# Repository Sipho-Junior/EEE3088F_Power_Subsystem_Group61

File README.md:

# EEE3088F_Power_Subsystem_Group61 
The micro-mouse project requires the design and development of a compact, efficient, and reliable power subsystem capable of operating autonomously within a constrained embedded system.
This subsystem will be interfaced with the rest of the micro-mouse through a 2x16-pin header and a JST PH connector for the battery, designed to comply with the physical and electrical constraints specified in the project brief. 

This repository contains the design files and documentation for the power subsystem of an autonomous micro-mouse project developed for EEE3088F 2025. The micro-mouse is designed to navigate and solve mazes autonomously.

# System Architecture
The complete micro-mouse consists of four essential subsystems:

Motherboard - The foundation PCB connecting all other components
Processor Board - Features an STM32L476 microcontroller for computation and control
Sensing Subsystem - Equipped with distance sensors for environmental awareness
Power Subsystem - Focus of this repository

# Power Subsystem Features
The power subsystem is responsible for:

Providing stable 3.3V and 5V power to all micro-mouse components
Controlling up to 4 motors bidirectionally (2 main motors + 2 auxiliary)
Supporting external load switching (2 channels at 1A each)
Real-time power monitoring via INA219 on I2C bus
Battery management for a 1S1P LiPo battery (800mAh 3.7V)
Dual charging modes (200mA and 600mA±100mA)
USB-C power input with 9V Power Delivery negotiation
Power system ON/OFF control with ultra-low standby current (<30μA)

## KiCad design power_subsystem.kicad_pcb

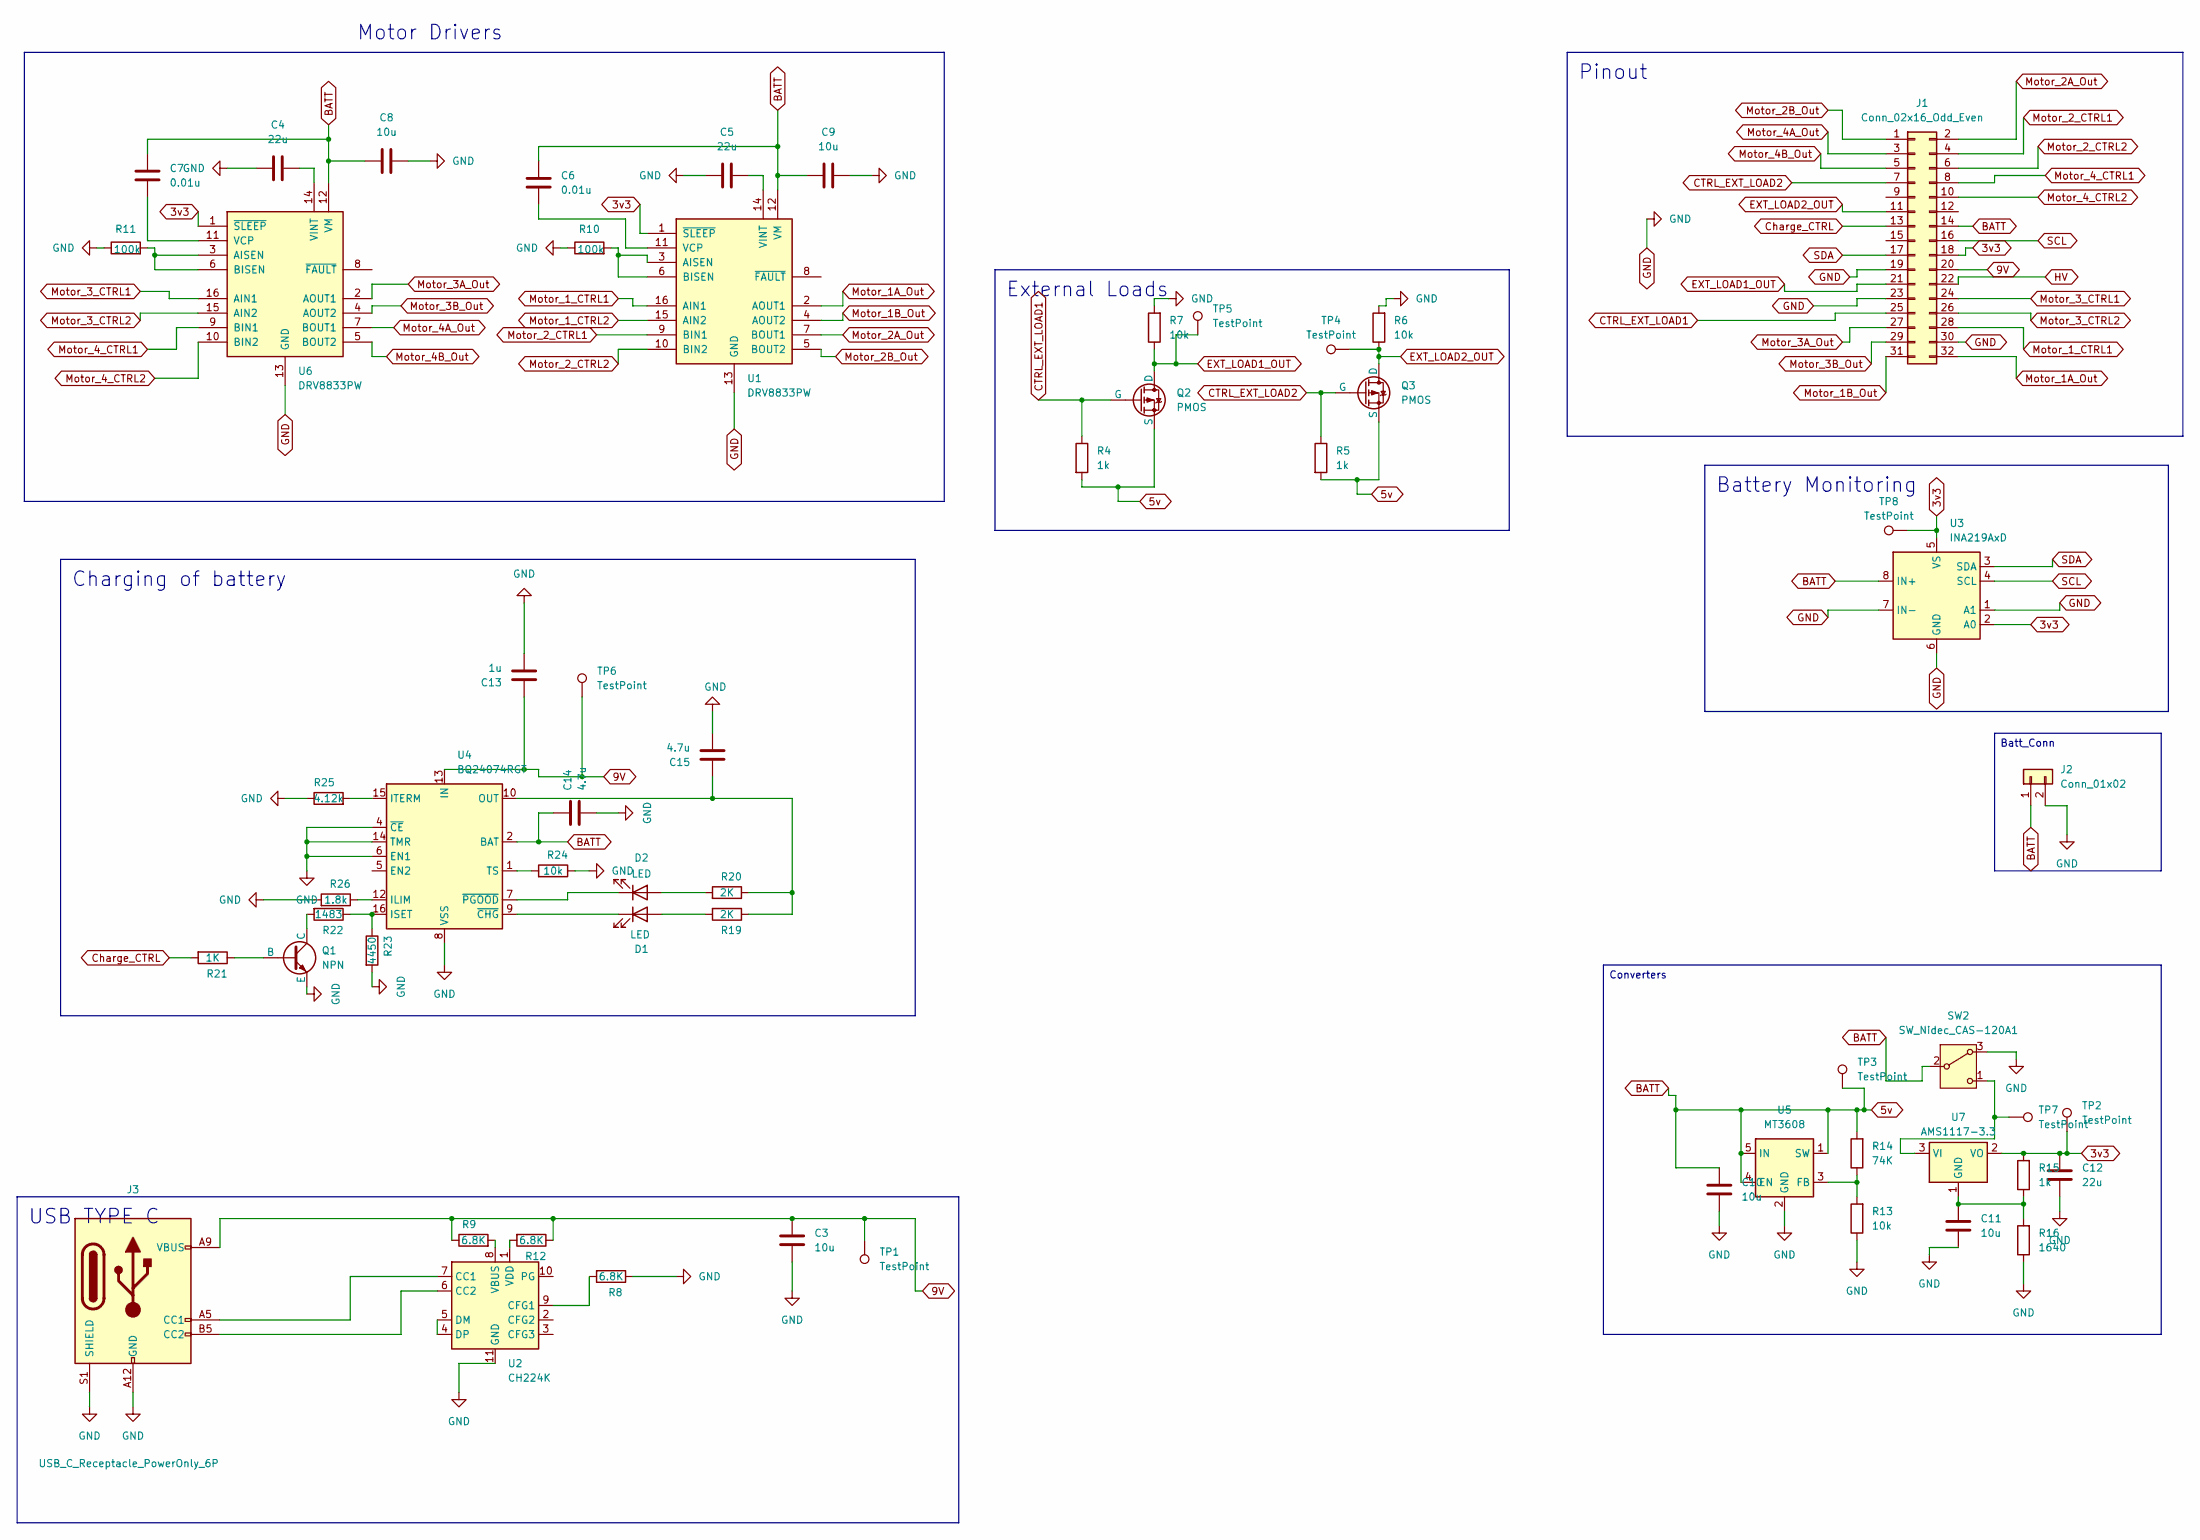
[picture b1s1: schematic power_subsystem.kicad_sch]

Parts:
C3, C8, C9, C10, C11: 10u; C_0201_0603Metric
C4, C5, C12: 22u; C_0201_0603Metric
C6, C7: 0.01u; C_0201_0603Metric
C13: 1u; C_0201_0603Metric
C14, C15: 4.7u; C_0201_0603Metric
D1, D2: LED; LED_0201_0603Metric
J1: Conn_02x16_Odd_Even; PinHeader_2x16_P2.54mm_Vertical
J2: Conn_01x02; JST_PH_S2B-PH-K_1x02_P2.00mm_Horizontal
J3: USB_C_Receptacle_PowerOnly_6P; USB_C_Receptacle_GCT_USB4125-xx-x-0190_6P_TopMnt_Horizontal
Q1: NPN; TO-92L_HandSolder
Q2, Q3: PMOS; TO-92L_Inline
R4, R5, R15: 1k; R_0201_0603Metric
R6, R7, R13, R24: 10k; R_0201_0603Metric
R8, R9, R12: 6.8K; R_0201_0603Metric
R10, R11: 100k; R_0201_0603Metric
R14: 74K; R_0201_0603Metric
R16: 1640; R_0201_0603Metric
R19, R20: 2K; R_0201_0603Metric
R21: 1K; R_0201_0603Metric
R22: 1483; R_0201_0603Metric
R23: 4450; R_0201_0603Metric
R25: 4.12k; R_0201_0603Metric
R26: 1.8k; R_0201_0603Metric
SW2: SW_Nidec_CAS-120A1; Nidec_Copal_CAS-120A
TP1, TP2, TP3, TP4, TP5, TP6, TP7, TP8: TestPoint; TestPoint_Pad_D1.5mm
U1, U6: DRV8833PW; TSSOP-16_4.4x5mm_P0.65mm
U2: CH224K; SSOP-10-1EP_3.9x4.9mm_P1mm_EP2.1x3.3mm
U3: INA219AxD; SOIC-8_3.9x4.9mm_P1.27mm
U4: BQ24074RGT; VQFN-16-1EP_3x3mm_P0.5mm_EP1.8x1.8mm
U5: MT3608; SOT-23-6
U7: AMS1117-3.3; SOT-223-3_TabPin2

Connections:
3v3: C12.2, J1.18, R15.2, TP2.1, TP8.1, U1.1 (~SLEEP), U3.2 (A0), U3.5 (VS), U6.1 (~SLEEP), U7.2 (VO)
5v: C6.1, C7.1, C8.1, C9.1, C10.2, C14.2, J1.14, J2.1, Q2.3 (S), Q3.3 (S), R4.2, R5.2, R14.2, SW2.2 (B), TP3.1, U1.12 (VM), U3.8 (IN+), U4.2 (BAT), U4.3 (BAT), U5.1 (SW), U5.4 (EN), U5.5 (IN), U6.12 (VM)
9V: C3.2, C13.2, J1.20, J3.A9 (VBUS), J3.B9 (VBUS), R9.1, R12.1, TP1.1, TP6.1, U4.13 (IN)
CTRL_EXT_LOAD1: J1.25, Q2.2 (G), R4.1
CTRL_EXT_LOAD2: J1.7, Q3.2 (G), R5.1
Charge_CTRL: J1.13, R21.2
EXT_LOAD1_OUT: J1.21, Q2.1 (D), R7.1, TP5.1
EXT_LOAD2_OUT: J1.11, Q3.1 (D), R6.1, TP4.1
GND: C3.1, C4.1, C5.1, C8.2, C9.2, C10.1, C11.1, C12.1, C13.1, C14.1, C15.1, J1.19, J1.23, J1.30, J2.2, J3.A12 (GND), J3.B12 (GND), J3.S1 (SHIELD), Q1.3 (E), R6.2, R7.2, R8.1, R10.1, R11.1, R13.1, R16.1, R23.2, R24.1, R25.1, R26.2, SW2.3 (A), U1.13 (GND), U2.11 (GND), U3.1 (A1), U3.6 (GND), U3.7 (IN-), U4.4 (~CE), U4.6 (EN1), U4.8 (VSS), U4.14 (TMR), U4.17 (VSS), U5.2 (GND), U6.13 (GND)
HV: J1.22
Motor_1A_Out: J1.32, U1.2 (AOUT1)
Motor_1B_Out: J1.31, U1.4 (AOUT2)
Motor_1_CTRL1: J1.28, U1.16 (AIN1)
Motor_1_CTRL2: U1.15 (AIN2)
Motor_2A_Out: J1.2, U1.7 (BOUT1)
Motor_2B_Out: J1.1, U1.5 (BOUT2)
Motor_2_CTRL1: J1.4, U1.9 (BIN1)
Motor_2_CTRL2: J1.6, U1.10 (BIN2)
Motor_3A_Out: J1.27, U6.2 (AOUT1)
Motor_3B_Out: J1.29, U6.4 (AOUT2)
Motor_3_CTRL1: J1.24, U6.16 (AIN1)
Motor_3_CTRL2: J1.26, U6.15 (AIN2)
Motor_4A_Out: J1.3, U6.7 (BOUT1)
Motor_4B_Out: J1.5, U6.5 (BOUT2)
Motor_4_CTRL1: J1.8, U6.9 (BIN1)
Motor_4_CTRL2: J1.10, U6.10 (BIN2)
unnamed: C15.2, R19.1, R20.1, U4.10 (OUT), U4.11 (OUT)
unnamed: D1.2 (A), R19.2
unnamed: D1.1 (K), U4.9 (~CHG)
unnamed: D2.2 (A), R20.2
unnamed: D2.1 (K), U4.7 (~PGOOD)
unnamed: J3.A5 (CC1), U2.7 (CC1)
unnamed: J3.B5 (CC2), U2.6 (CC2)
unnamed: Q1.2 (B), R21.1
unnamed: Q1.1 (C), R22.2
unnamed: SW2.1 (C), TP7.1, U7.3 (VI)
unnamed: R10.2, U1.3 (AISEN), U1.6 (BISEN)
unnamed: C6.2, U1.11 (VCP)
unnamed: C5.2, U1.14 (VINT)
unnamed: R8.2, U2.9 (CFG1)
unnamed: U2.4 (DP), U2.5 (DM)
unnamed: R9.2, U2.8 (VBUS)
unnamed: R12.2, U2.1 (VDD)
unnamed: R26.1, U4.12 (ILIM)
unnamed: R22.1, R23.1, U4.16 (ISET)
unnamed: R25.2, U4.15 (ITERM)
unnamed: R24.2, U4.1 (TS)
unnamed: R13.2, R14.1, U5.3 (FB)
unnamed: R11.2, U6.3 (AISEN), U6.6 (BISEN)
unnamed: C7.2, U6.11 (VCP)
unnamed: C4.2, U6.14 (VINT)
unnamed: C11.2, R15.1, R16.2, U7.1 (GND)
SCL: J1.16, U3.4 (SCL)
SDA: J1.17, U3.3 (SDA)

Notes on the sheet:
Motor Drivers
Converters
USB TYPE C
Charging of battery
Pinout
External Loads
Battery Monitoring
Batt_Conn

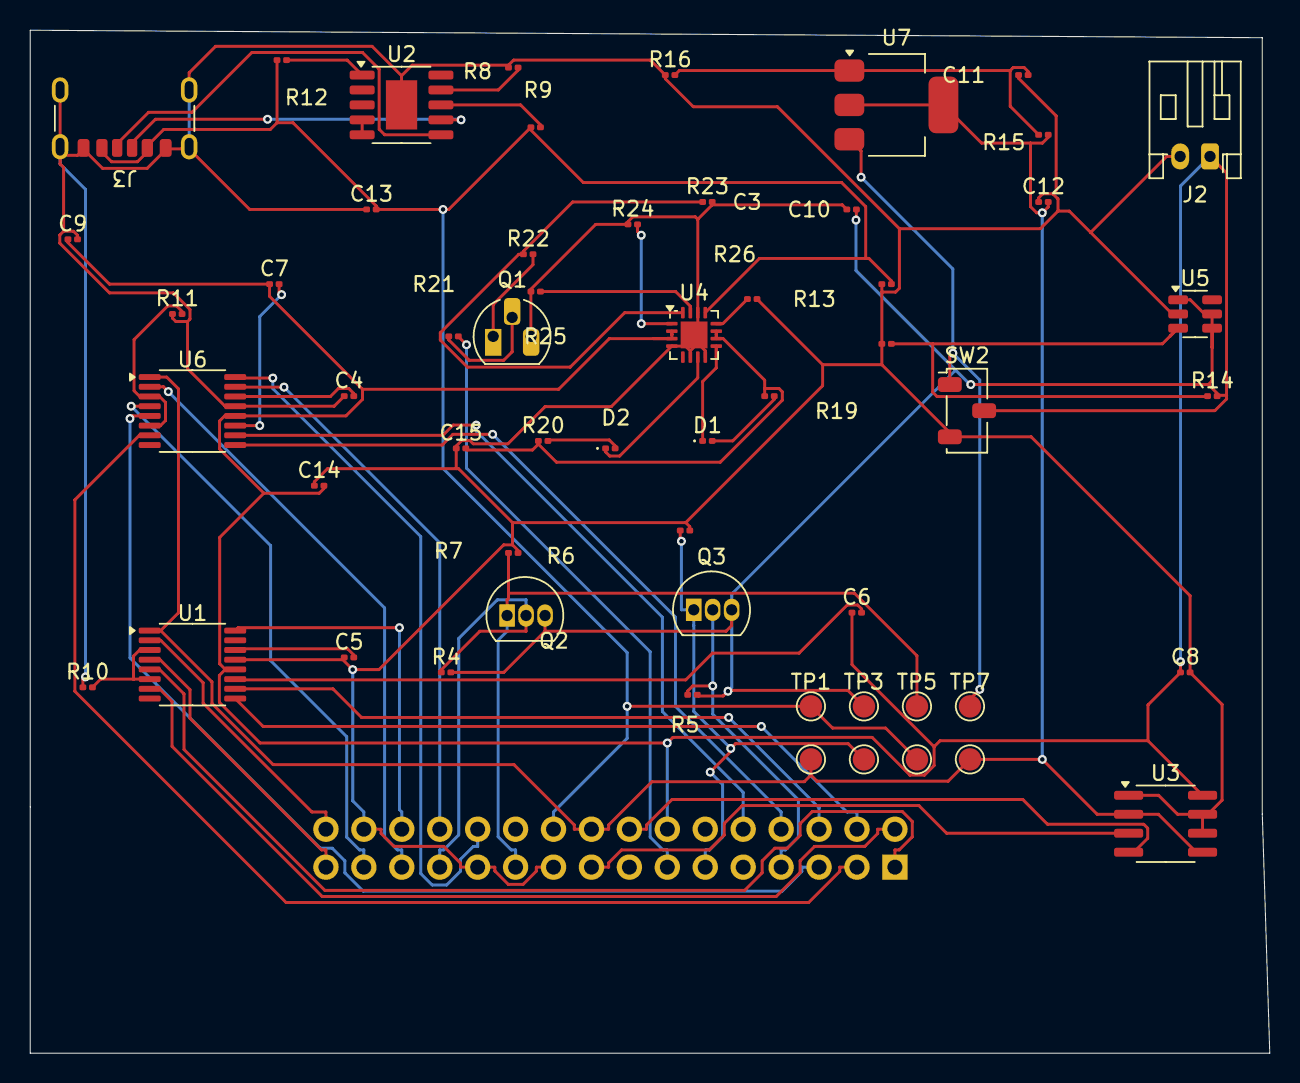
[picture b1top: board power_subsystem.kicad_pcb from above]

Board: 2 copper layers, 83.0 x 68.5 mm, 58 parts (1 on the bottom side), 52 nets.

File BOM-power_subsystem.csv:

Comment,Designator,Footprint,LCSC,Quantity
SW_Nidec_CAS-120A1,SW2,Nidec_Copal_CAS-120A,C115374,1
22u,C12,C_0201_0603Metric,C12891,1
INA219AxD,U3,SOIC-8_3.9x4.9mm_P1.27mm,C138706,1
10k,"R13,R24,R6,R7",R_0201_0603Metric,C17414,4
6.8K,"R12,R8,R9",R_0201_0603Metric,C17772,3
4.7u,"C14,C15",C_0201_0603Metric,C1779,2
74K,R14,R_0201_0603Metric,C17801,1
100k,"R10,R11",R_0201_0603Metric,C17900,2
4450,"R23,R25",R_0201_0603Metric,C1980,2
NPN,Q1,TO-92L_HandSolder,C2145,1
LED,D1,LED_0201_0603Metric,C2296,1
LED,D2,LED_0201_0603Metric,C2297,1
PMOS,"Q2,Q3",TO-92L_Inline,C2564,2
0.01u,"C6,C7",C_0201_0603Metric,C38523,2
USB_C_Receptacle_PowerOnly_6P,J3,USB_C_Receptacle_GCT_USB4125-xx-x-0190_6P_TopMnt_Horizontal,C399924,1
2K,"R19,R20",R_0201_0603Metric,C4109,2
1.8k,R26,R_0201_0603Metric,C4177,1
1640,"R16,R22",R_0201_0603Metric,C4310,2
1k,"R15,R21,R4,R5",R_0201_0603Metric,C4410,4
22u,"C4,C5",C_0201_0603Metric,C45783,2
AMS1117-3.3,U7,SOT-223-3_TabPin2,C5120796,1
BQ24074RGT,U4,VQFN-16-1EP_3x3mm_P0.5mm_EP1.8x1.8mm,C54313,1
DRV8833PW,"U1,U6",TSSOP-16_4.4x5mm_P0.65mm,C544801,2
10u,"C10,C11,C13,C3,C8,C9",C_0201_0603Metric,C7171,6
MT3608,U5,SOT-23-6,C84817,1
CH224K,U2,SSOP-10-1EP_3.9x4.9mm_P1mm_EP2.1x3.3mm,C970725,1
